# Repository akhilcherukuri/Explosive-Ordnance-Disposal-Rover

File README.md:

# Explosive Ordnance Disposal Rover

Final Year Major Project for Electronics and Communication Engineering

Youtube Link: https://youtu.be/dQHEDaG9FYA

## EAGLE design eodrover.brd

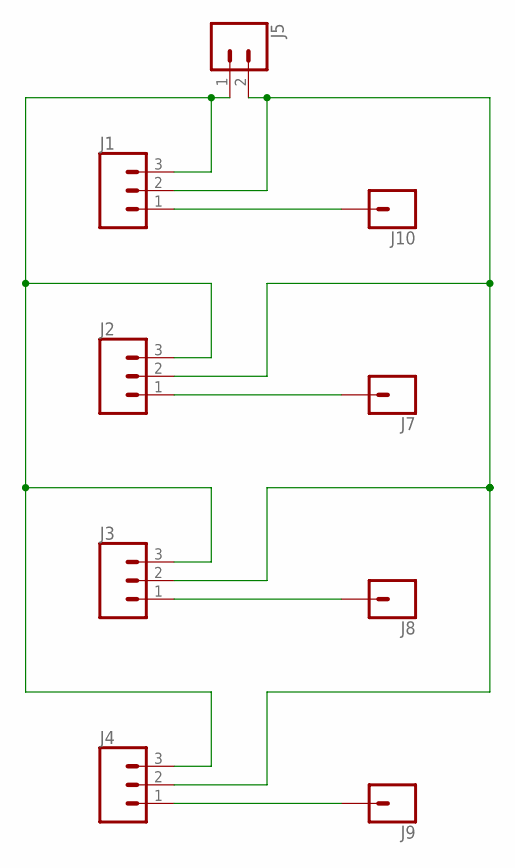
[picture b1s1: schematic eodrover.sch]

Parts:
J1, J2, J3, J4: CONN_03; 1X03
J5: CONN_02; 1X02
J7, J8, J9, J10: CONN_01; 1X01

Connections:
GND: J1.3, J2.3, J3.3, J4.3, J5.1
unnamed: J1.1, J10.1
unnamed: J2.1, J7.1
unnamed: J3.1, J8.1
unnamed: J4.1, J9.1
unnamed: J1.2, J2.2, J3.2, J4.2, J5.2

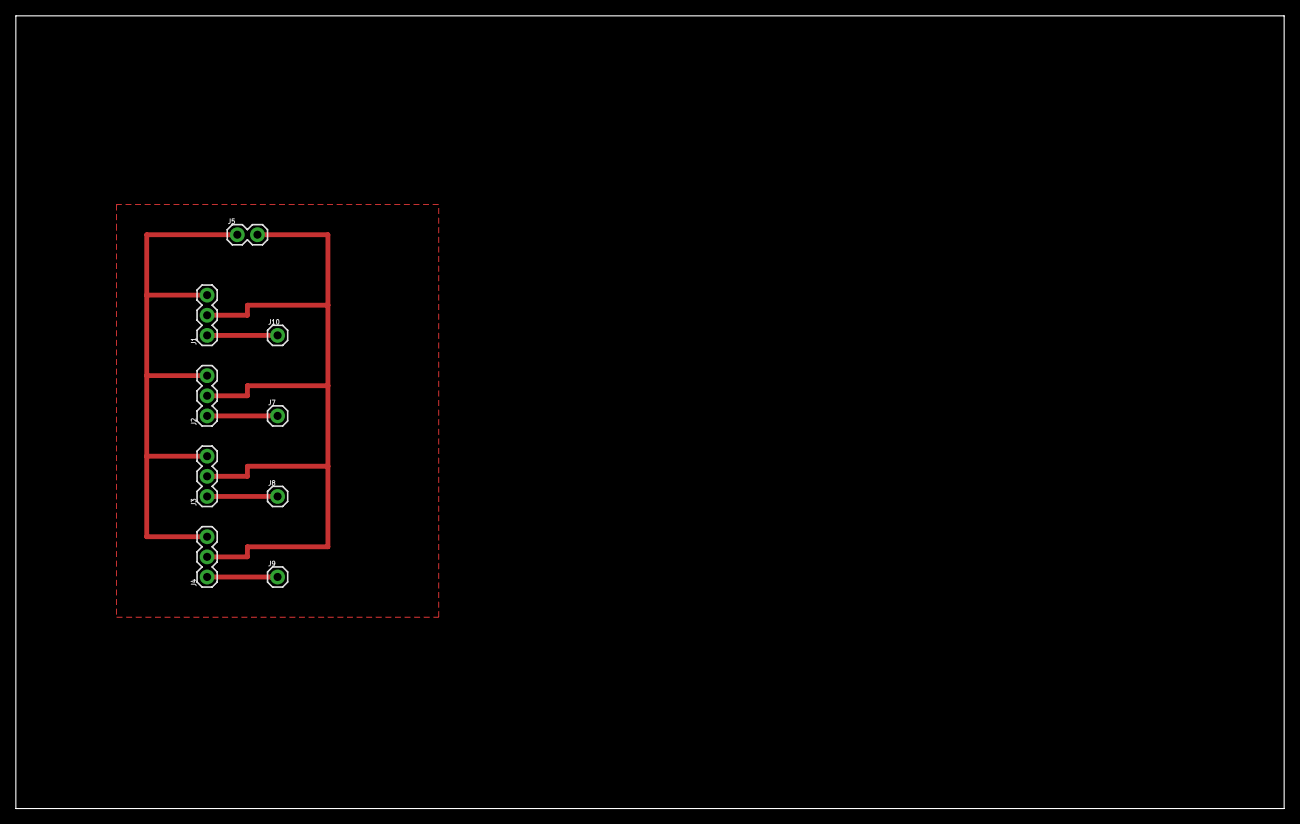
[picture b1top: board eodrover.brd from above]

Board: 2 copper layers, 160.0 x 100.0 mm, 9 parts (0 on the bottom side), 6 nets.

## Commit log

2020-10-09 Added Necessary Files for Review
2020-10-09 Added Images and Videos

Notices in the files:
parts and their libraries:
SparkFun-Connectors: Licensing: Creative Commons ShareAlike 4.0 International - https://creativecommons.org/licenses/by-sa/4.0
